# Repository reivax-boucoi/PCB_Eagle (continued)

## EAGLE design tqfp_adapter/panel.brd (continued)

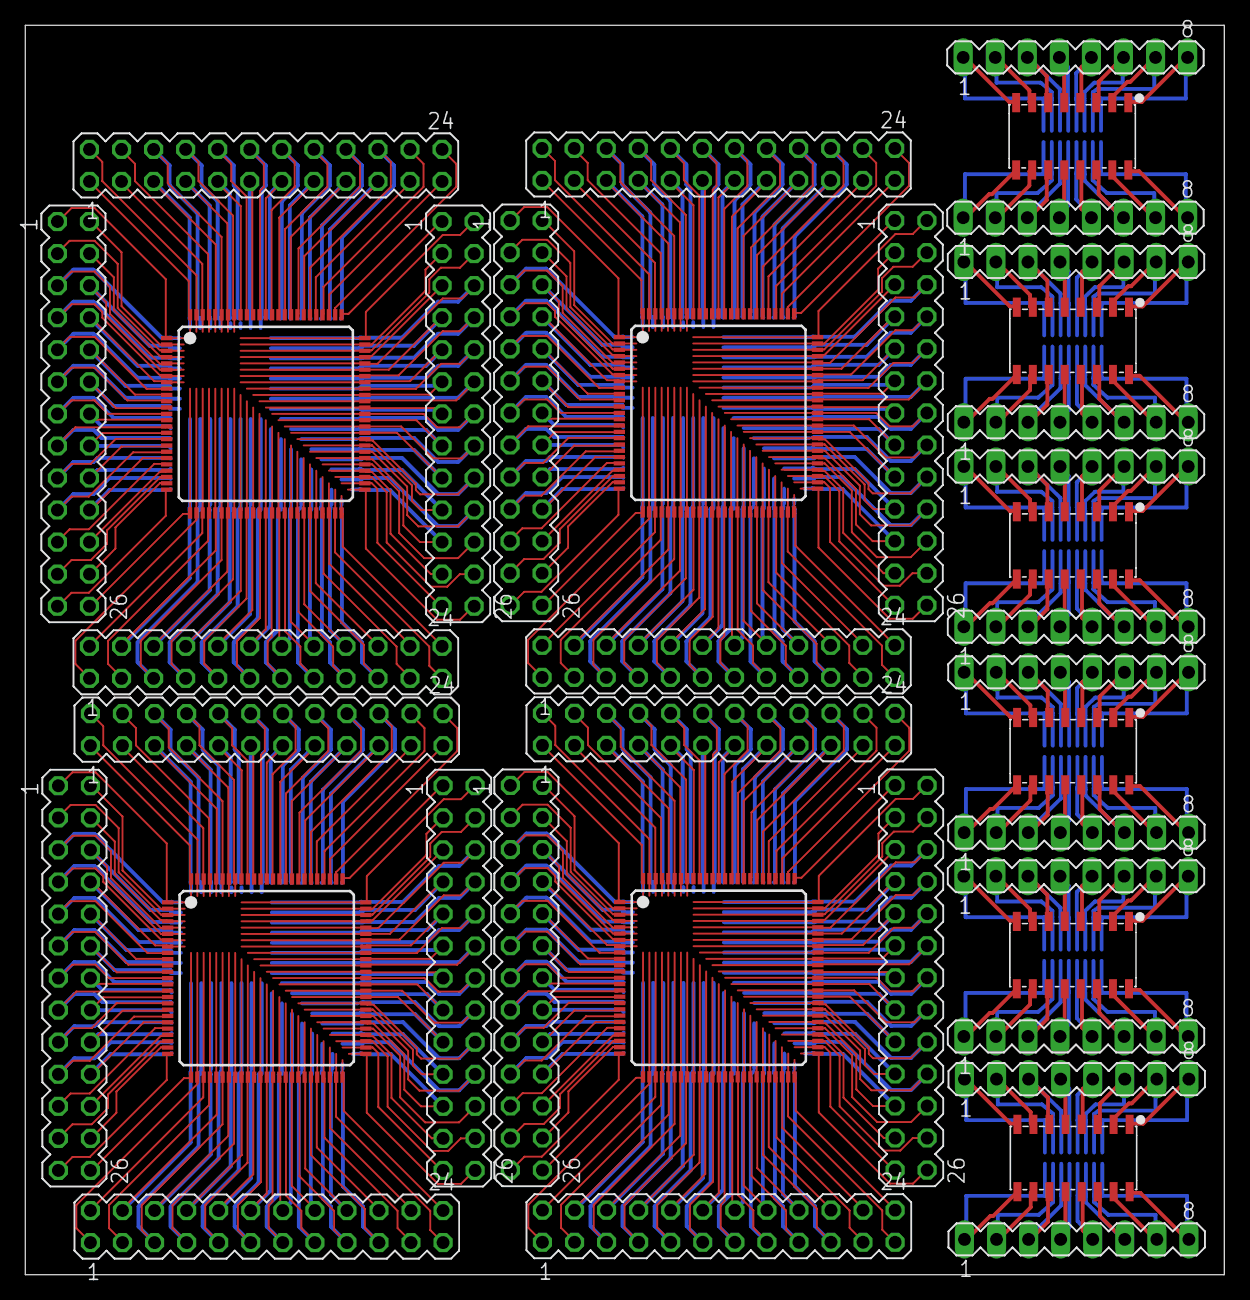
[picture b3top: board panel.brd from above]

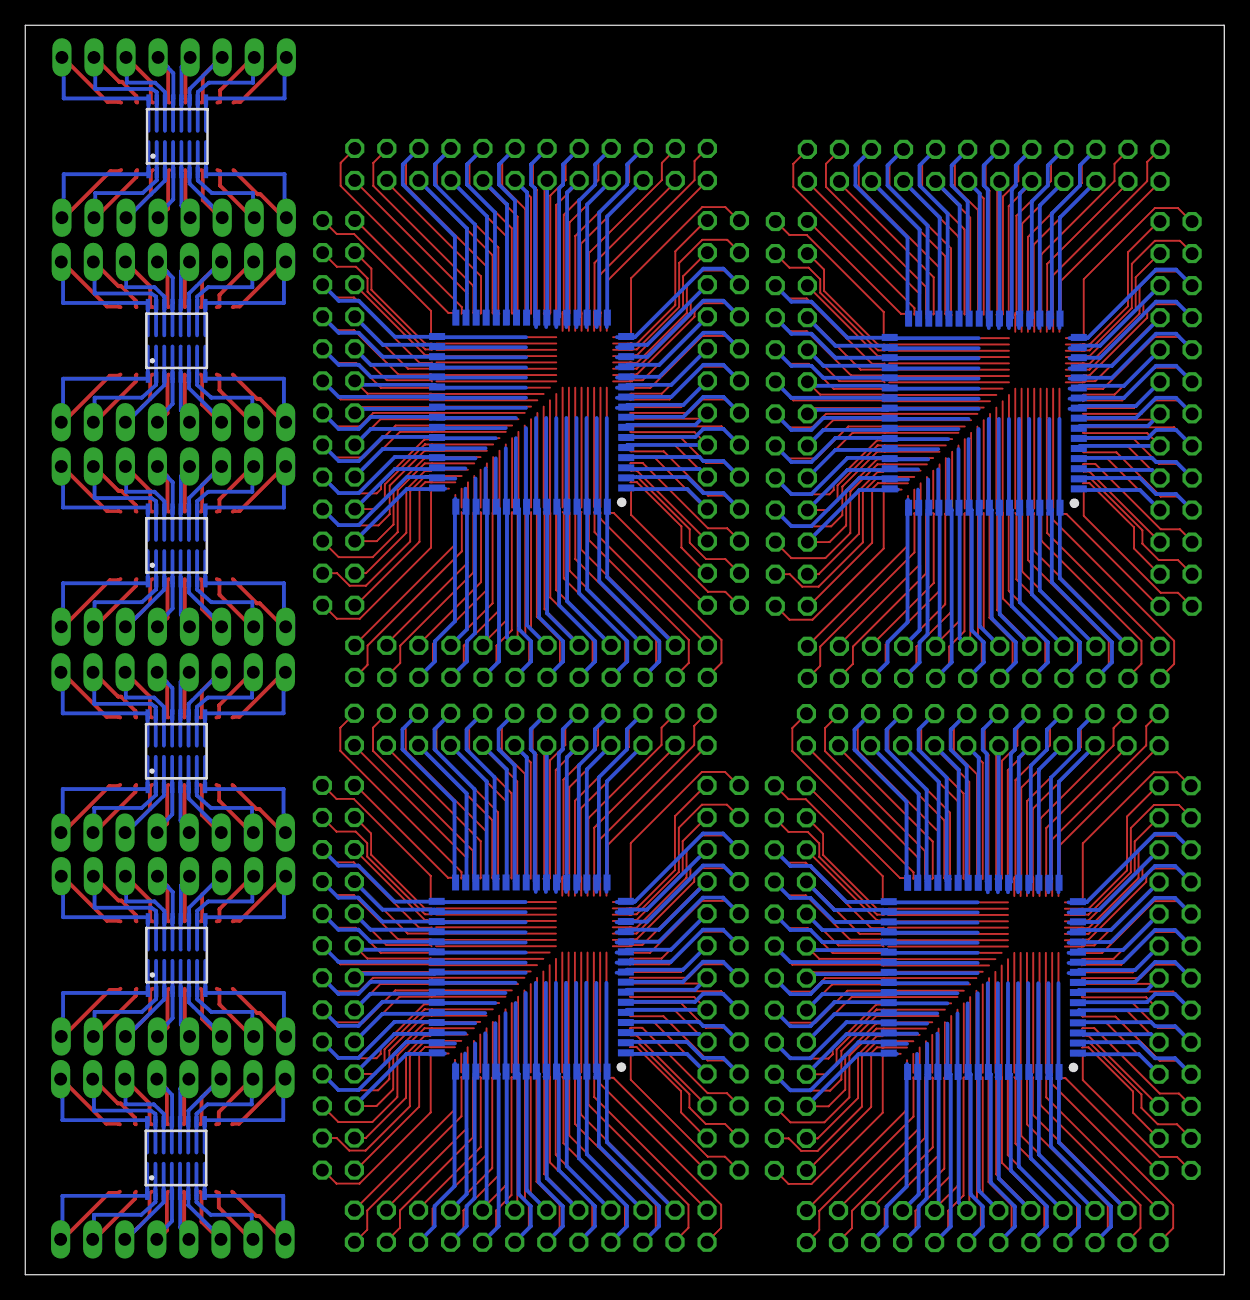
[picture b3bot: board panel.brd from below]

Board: 2 copper layers, 95.0 x 99.0 mm, 48 parts (10 on the bottom side), 486 nets.

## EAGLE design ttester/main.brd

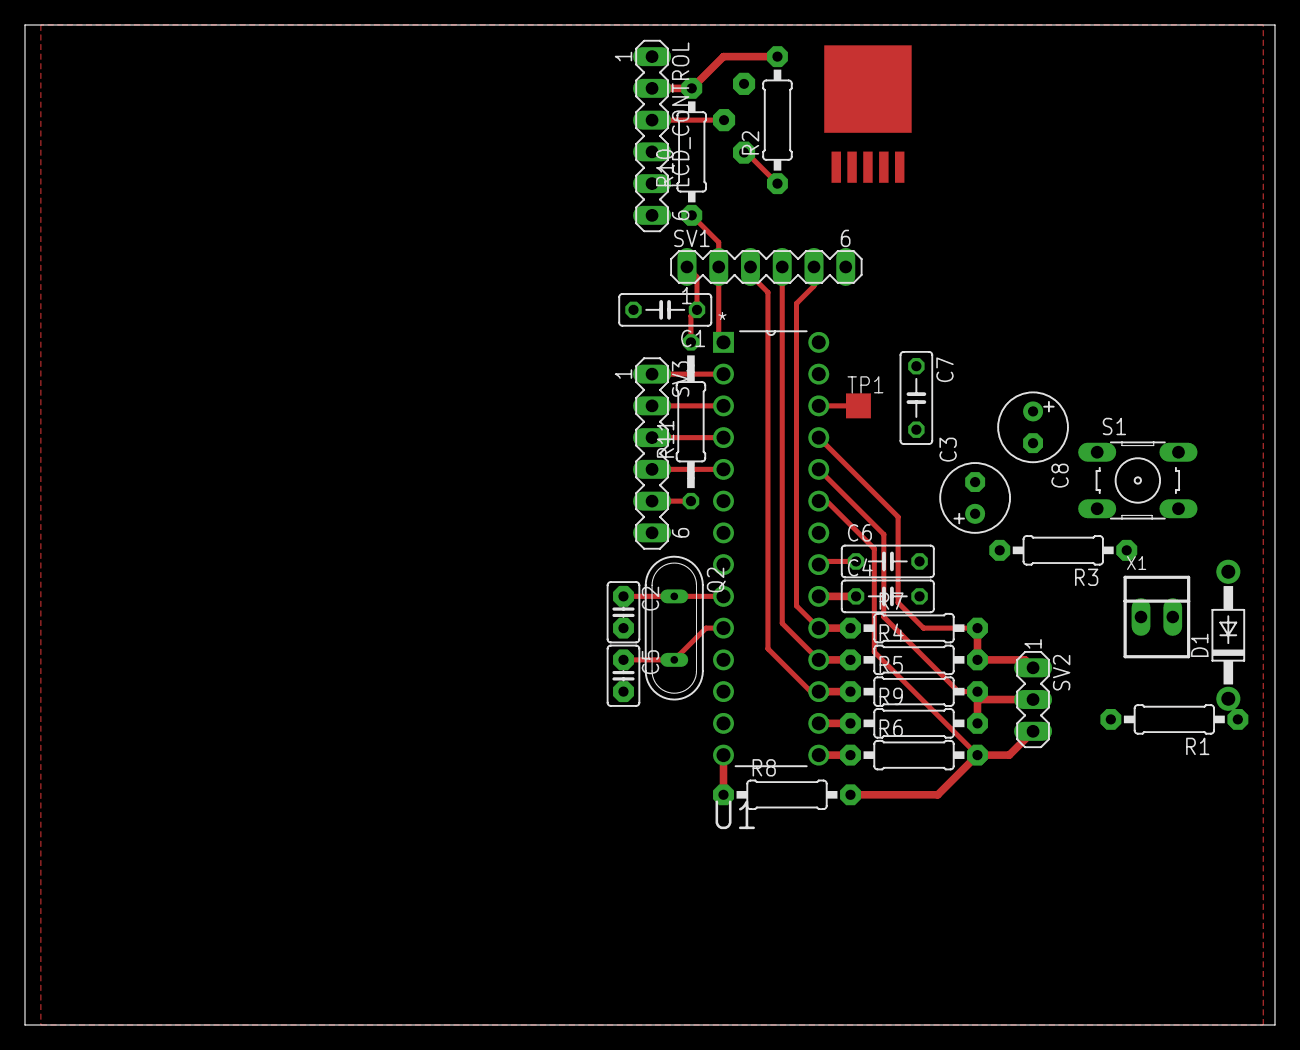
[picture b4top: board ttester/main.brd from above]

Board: 2 copper layers, 100.0 x 80.0 mm, 31 parts (1 on the bottom side), 28 nets.

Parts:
C1, C7: 100n; C050-025X075
C2, C5: 22p; C025-025X050
C3, C8: 10u; E2,5-6
C4: 10n; C050-025X075
C6: 1n; C050-025X075
D1: 1N4004; DO41-10
LCD_CONTROL: MA06-1
Q2: 16M; QS
R1: 1k; 0207/10
R2, R10: 10k; 0207/10
R3: 3k; 0207/10
R4, R8, R9: 680; 0207/10
R5, R6, R7: 470k; 0207/10
R11: 150; 0207/12
S1: B3F-10XX
SV1, SV3: MA06-1
SV2: MA03-1
TP1: TPTP20SQ; TP20SQ
U1: ATMEGA328P-PU; DIP254P762X457-28
U$1: POTAR
U$2: NJM2389; DPACK-5
X1: 22-23-2021

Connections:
+5V1: C8.+, D1.C, U$2.VIN
A: R11.1, SV3.5
AREF: C6.1, U1.21
D4: SV3.1, U1.2
D5: SV3.2, U1.3
D6: SV3.3, U1.4
D7: SV3.4, U1.5
E: LCD_CONTROL.6, U1.11
GND: C1.2, C2.2, C3.-, C4.2, C5.2, C6.2, C7.2, C8.-, LCD_CONTROL.1, R1.1, SV1.6, SV3.6, U1.8, U1.22, U$1.P$1, U$2.GND, X1.1
MISO: R4.1, SV1.4, U1.18
MOSI: R5.1, SV1.3, U1.17
unnamed: R2.1, U$1.P$2
unnamed: TP1.TP, U1.26
unnamed: R1.2, R3.1, U$2.VADJ
unnamed: R8.1, U1.14
unnamed: R6.1, U1.15
unnamed: R9.1, U1.16
RESET: R10.1, SV1.2, U1.1
RS: LCD_CONTROL.4, U1.6
SCK: R7.1, SV1.5, U1.19
TP1: R6.2, R8.2, SV2.3, U1.23
TP2: R5.2, R9.2, SV2.2, U1.24
TP3: R4.2, R7.2, SV2.1, U1.25
VBAT: D1.A, X1.2
VCC: C1.1, C3.+, C4.1, C7.1, LCD_CONTROL.2, R2.2, R3.2, R10.2, R11.2, SV1.1, U1.7, U1.20, U$2.VOUT, U$2.VOUT1
VO: LCD_CONTROL.3, U$1.WIPER
XTAL1: C2.1, Q2.1, U1.9
XTAL2: C5.1, Q2.2, U1.10

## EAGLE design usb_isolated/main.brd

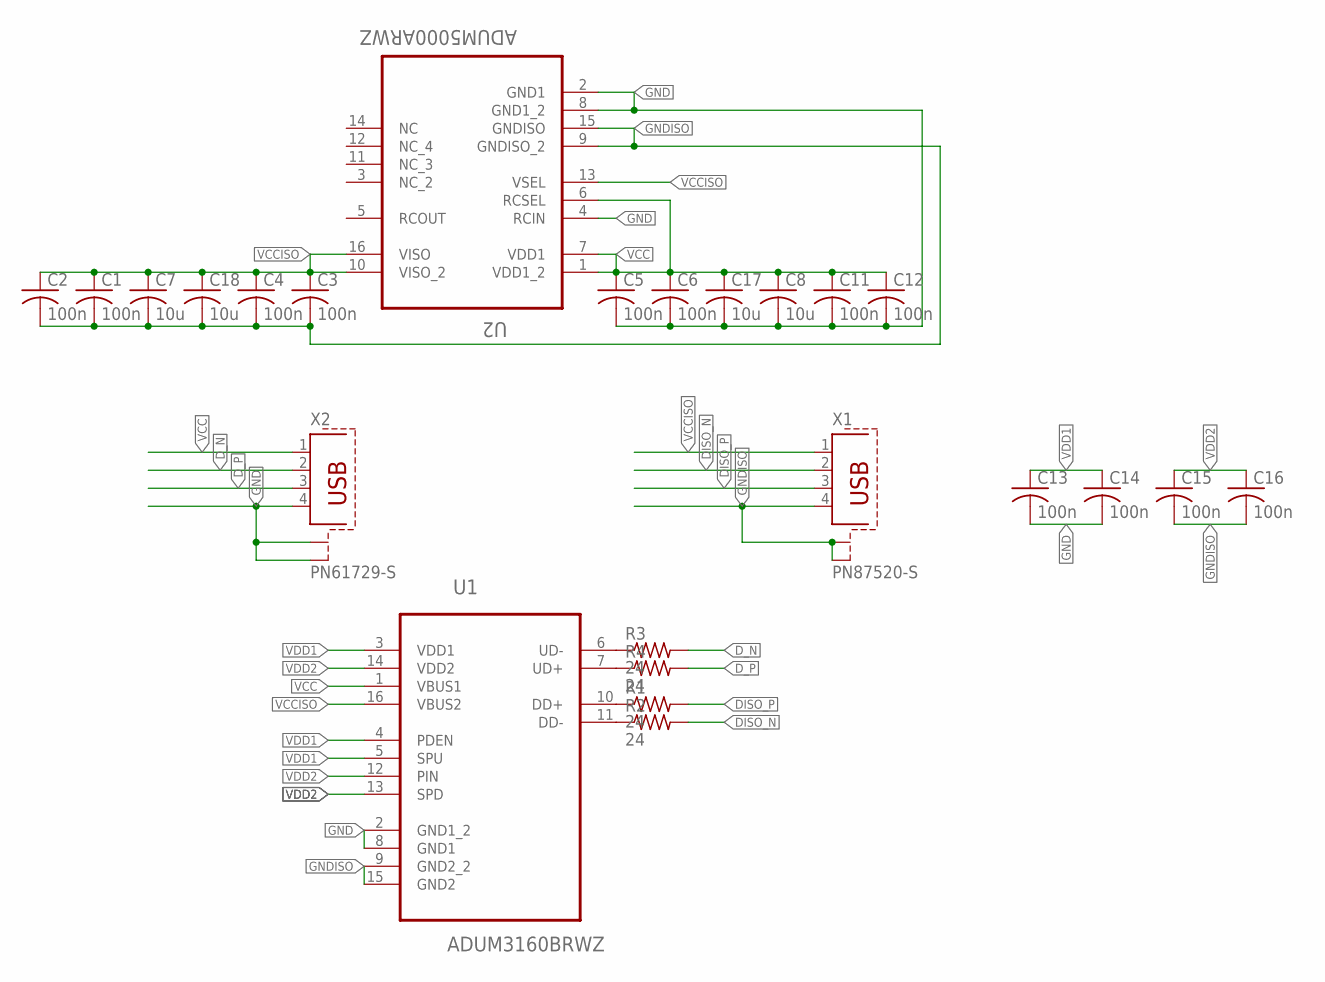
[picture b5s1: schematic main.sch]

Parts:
C1, C2, C3, C4, C5, C6, C11, C12, C13, C14, C15, C16: 100n; C0603
C7, C8, C17, C18: 10u; C025-025X050
R1, R2, R3, R4: 24; R0603
U1: ADUM3160BRWZ; SOIC127P1032X265-16N
U2: ADUM5000ARWZ; SOIC127P1032X265-16N
X1: PN87520-S
X2: PN61729-S

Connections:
DISO_N: R2.2, X1.2
DISO_P: R1.2, X1.3
D_N: R3.2, X2.2
D_P: R4.2, X2.3
GND: C5.2, C6.2, C8.2, C11.2, C12.2, C13.2, C14.2, C17.2, U1.2 (GND1_2), U1.8 (GND1), U2.2 (GND1), U2.4 (RCIN), U2.8 (GND1_2), X2.4, X2.S1, X2.S2
GNDISO: C1.2, C2.2, C3.2, C4.2, C7.2, C15.2, C16.2, C18.2, U1.9 (GND2_2), U1.15 (GND2), U2.9 (GNDISO_2), U2.15 (GNDISO), X1.4, X1.S1, X1.S2
unnamed: R1.1, U1.10 (DD+)
unnamed: R2.1, U1.11 (DD-)
unnamed: R3.1, U1.6 (UD-)
unnamed: R4.1, U1.7 (UD+)
VCC: C5.1, C6.1, C8.1, C11.1, C12.1, C17.1, U1.1 (VBUS1), U2.1 (VDD1_2), U2.6 (RCSEL), U2.7 (VDD1), X2.1
VCCISO: C1.1, C2.1, C3.1, C4.1, C7.1, C18.1, U1.16 (VBUS2), U2.10 (VISO_2), U2.13 (VSEL), U2.16 (VISO), X1.1
VDD1: C13.1, C14.1, U1.3 (VDD1), U1.4 (PDEN), U1.5 (SPU)
VDD2: C15.1, C16.1, U1.12 (PIN), U1.13 (SPD), U1.14 (VDD2)

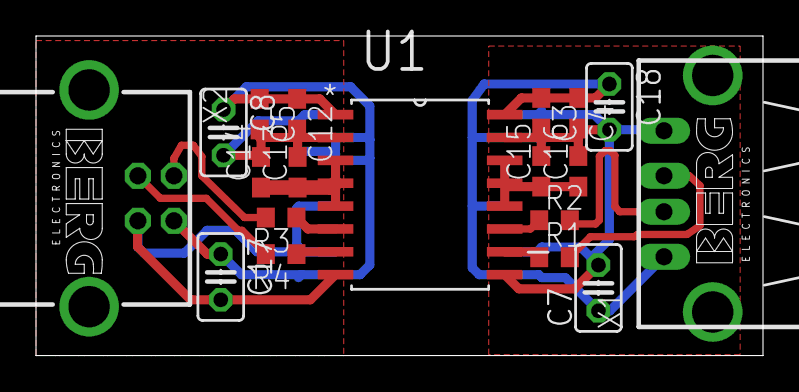
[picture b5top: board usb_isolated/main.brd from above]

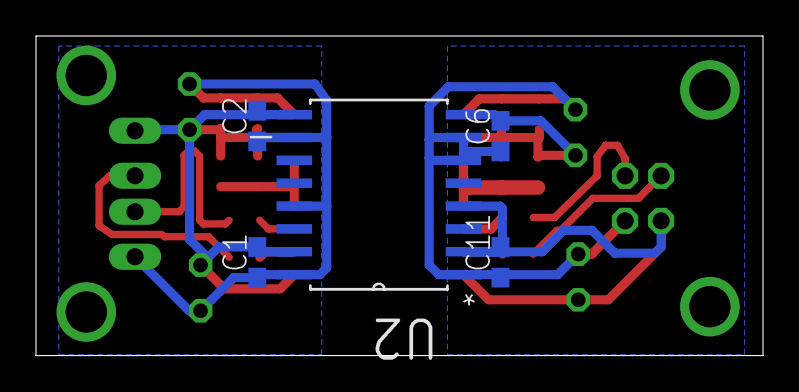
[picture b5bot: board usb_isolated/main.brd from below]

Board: 2 copper layers, 40.4 x 17.8 mm, 24 parts (5 on the bottom side), 14 nets.

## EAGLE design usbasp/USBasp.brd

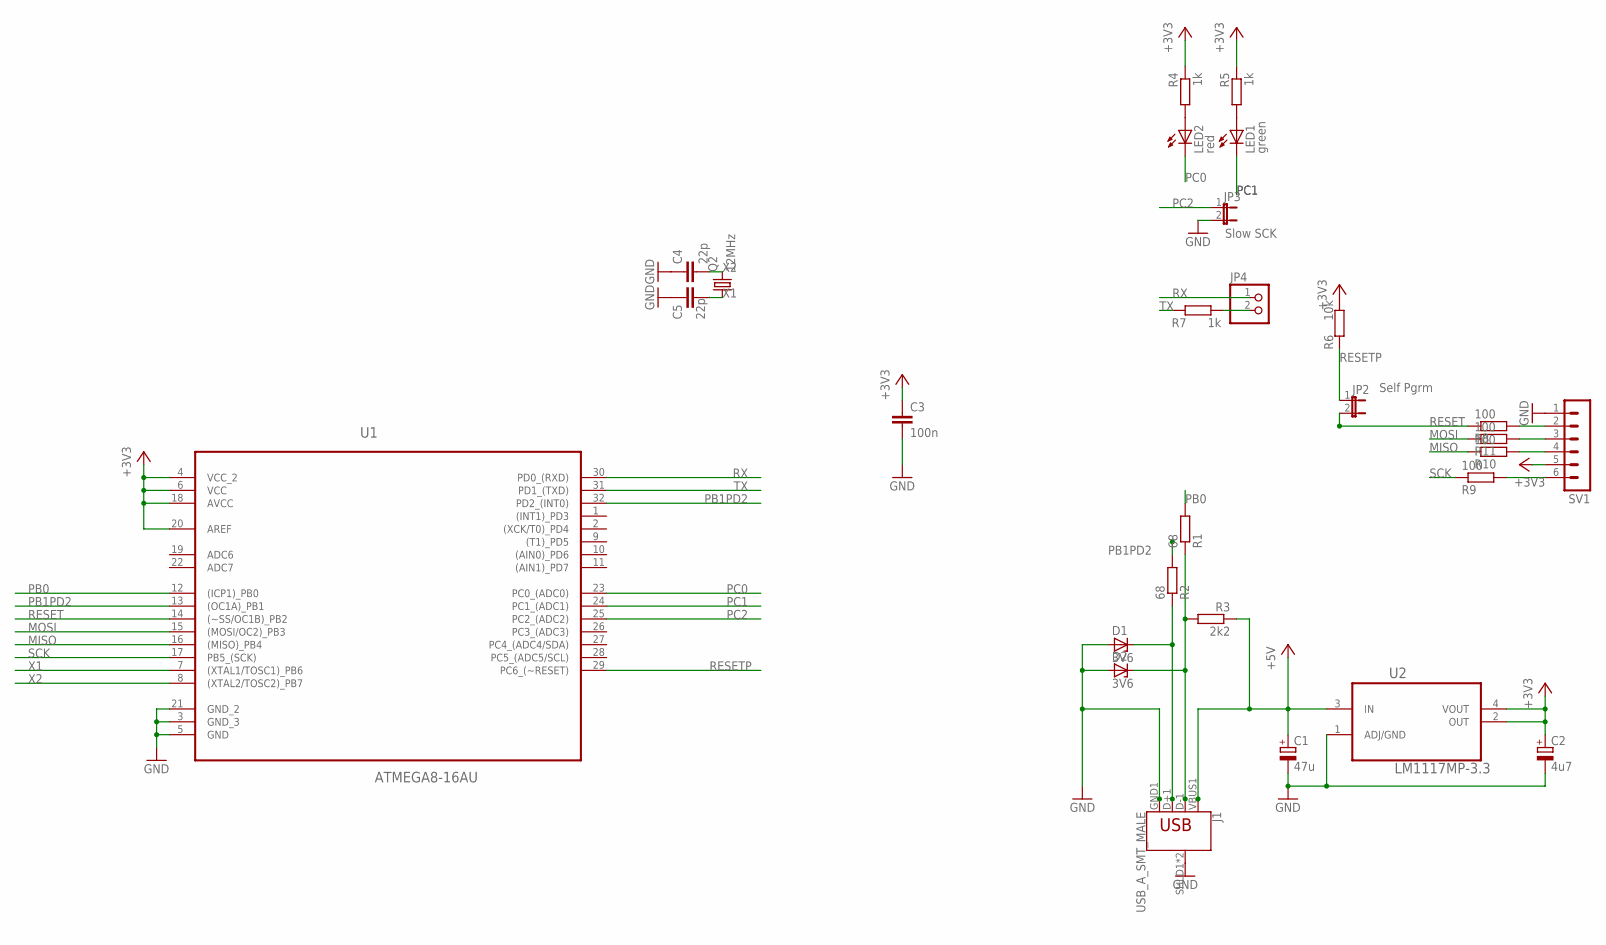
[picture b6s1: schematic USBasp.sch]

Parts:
C1: 47u; ETR4
C2: 4u7; E2,5-5
C3: 100n; C0603
C4: 22p; C0603
C5: 22p; C0504
D1, D2: 3V6; SOD80C
J1: USB_A_SMT_MALE; USB-A-SMT-MALE
JP2: Self Pgrm; JP1
JP3: Slow SCK; JP1
JP4: PINHD-1X2; 1X02
LED1: green; CHIP-LED0603
LED2: red; CHIP-LED0603
Q2: 12MHz; HC49/S
R1, R2: 68; R0603
R3: 2k2; R0603
R4, R5, R7: 1k; R0603
R6: 10k; R0603
R8, R9, R10, R11: 100; R0603
SV1: MA06-1
U1: ATMEGA8-16AU; QFP80P900X900X120-32N
U2: LM1117MP-3.3; SOT230P696X180-4N

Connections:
+3V3: C2.+, C3.1, R4.1, R5.1, R6.1, SV1.5, U1.4 (VCC_2), U1.6 (VCC), U1.18 (AVCC), U1.20 (AREF), U2.2 (OUT), U2.4 (VOUT)
+5V: C1.+, J1.VBUS1 (VBUS), R3.1, U2.3 (IN)
GND: C1.-, C2.-, C3.2, C4.1, C5.1, D1.A, D2.A, J1.GND1 (GND), J1.SHLD1 (SHIELD), J1.SHLD2 (SHIELD), JP3.2, SV1.1, U1.3 (GND_3), U1.5 (GND), U1.21 (GND_2), U2.1 (ADJ/GND)
MISO: R10.1, U1.16 ((MISO)_PB4)
MOSI: R11.1, U1.15 ((MOSI/OC2)_PB3)
unnamed: D2.C, J1.D-1 (D-), R1.1, R3.2
unnamed: D1.C, J1.D+1 (D+), R2.1
unnamed: JP4.2, R7.1
unnamed: LED2.A, R4.2
unnamed: R8.2, SV1.2
unnamed: R9.2, SV1.6
unnamed: R10.2, SV1.4
unnamed: R11.2, SV1.3
unnamed: LED1.A, R5.2
PB0: R1.2, U1.12 ((ICP1)_PB0)
PB1PD2: R2.2, U1.13 ((OC1A)_PB1), U1.32 (PD2_(INT0))
PC0: LED2.C, U1.23 (PC0_(ADC0))
PC1: LED1.C, U1.24 (PC1_(ADC1))
PC2: JP3.1, U1.25 (PC2_(ADC2))
RESET: JP2.2, R8.1, U1.14 ((~SS/OC1B)_PB2)
RESETP: JP2.1, R6.2, U1.29 (PC6_(~RESET))
RX: JP4.1, U1.30 (PD0_(RXD))
SCK: R9.1, U1.17 (PB5_(SCK))
TX: R7.2, U1.31 (PD1_(TXD))
X1: C5.2, Q2.1, U1.7 ((XTAL1/TOSC1)_PB6)
X2: C4.2, Q2.2, U1.8 ((XTAL2/TOSC2)_PB7)

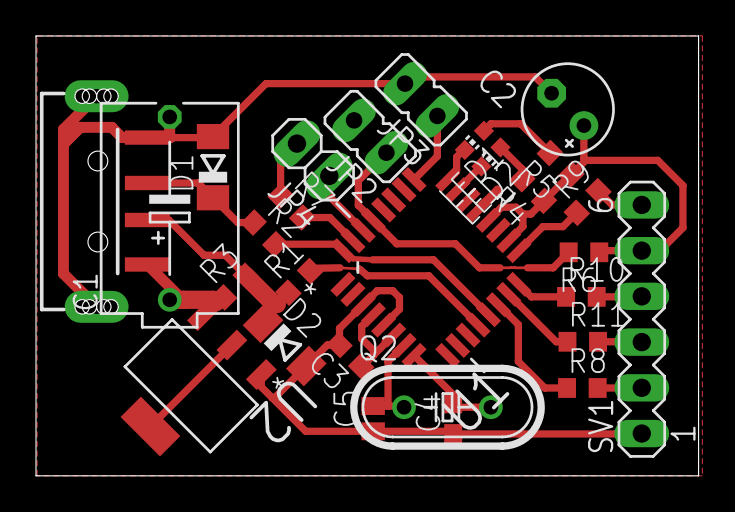
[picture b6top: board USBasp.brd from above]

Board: 2 copper layers, 36.8 x 24.4 mm, 28 parts (0 on the bottom side), 26 nets.

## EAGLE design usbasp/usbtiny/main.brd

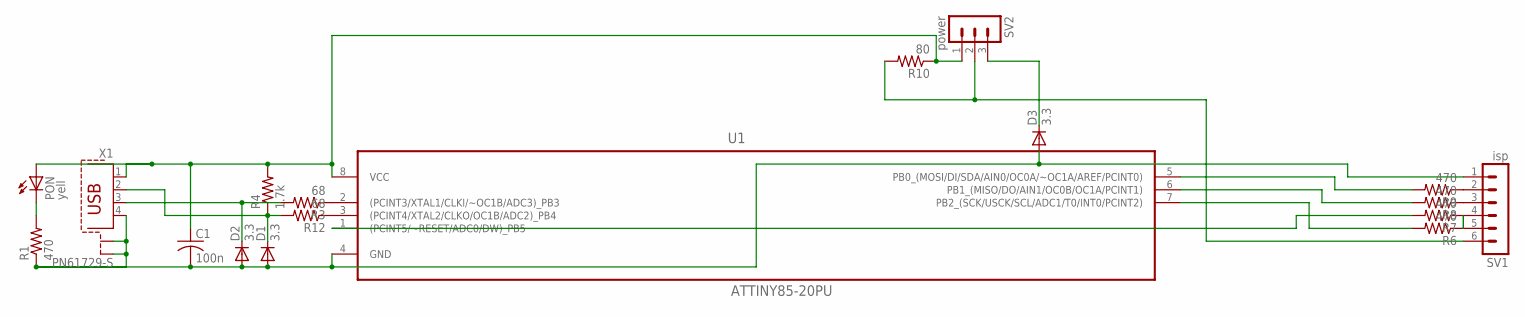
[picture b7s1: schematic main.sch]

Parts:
C1: 100n; C0805K
D1, D2, D3: 3.3; MELF-MLL41
PON: yell; LED5MM
R1, R6, R8, R9: 470; R0805
R3, R12: 68; R0805
R4: 1.7k; R0805
R7: 470; 0207/12
R10: 80; R0805
SV1: isp; MA06-1
SV2: power; MA03-1
U1: ATTINY85-20PU; DIP254P762X533-8
X1: PN61729-S

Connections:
unnamed: D1.C, R4.1, R12.2, X1.2
unnamed: R3.1, U1.2 ((PCINT3/XTAL1/CLKI/~OC1B/ADC3)_PB3)
unnamed: R12.1, U1.3 ((PCINT4/XTAL2/CLKO/OC1B/ADC2)_PB4)
unnamed: R9.2, U1.5 (PB0_(MOSI/DI/SDA/AIN0/OC0A/~OC1A/AREF/P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)
unnamed: D2.C, R3.2, X1.3
unnamed: C1.2, D1.A, D2.A, D3.A, R1.1, SV1.1, U1.4 (GND), X1.4, X1.S1, X1.S2
unnamed: R8.2, U1.6 (PB1_(MISO/DO/AIN1/OC0B/OC1A/PCINT1))
unnamed: R6.2, U1.7 (PB2_(SCK/USCK/SCL/ADC1/T0/INT0/PCINT2))
unnamed: R9.1, SV1.2
unnamed: PON.K (C), R1.2
unnamed: R7.2, U1.1 ((PCINT5/~RESET/ADC0/DW)_PB5)
unnamed: R8.1, SV1.3
unnamed: R7.1, SV1.5
unnamed: R6.1, SV1.4
unnamed: D3.C, SV2.3
unnamed: R10.2, SV1.6, SV2.2
unnamed: C1.1, PON.A, R4.2, R10.1, SV2.1, U1.8 (VCC), X1.1

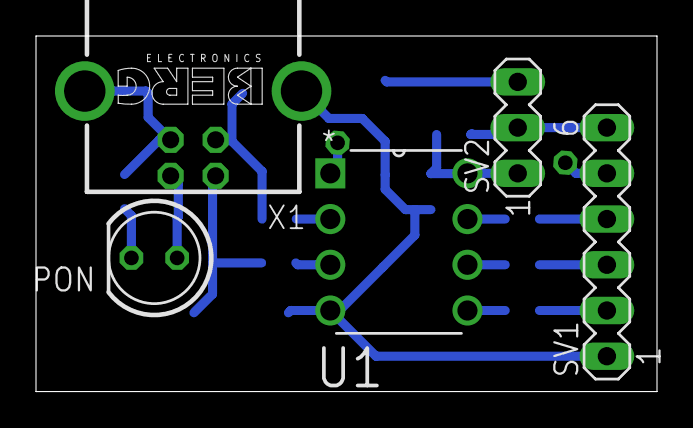
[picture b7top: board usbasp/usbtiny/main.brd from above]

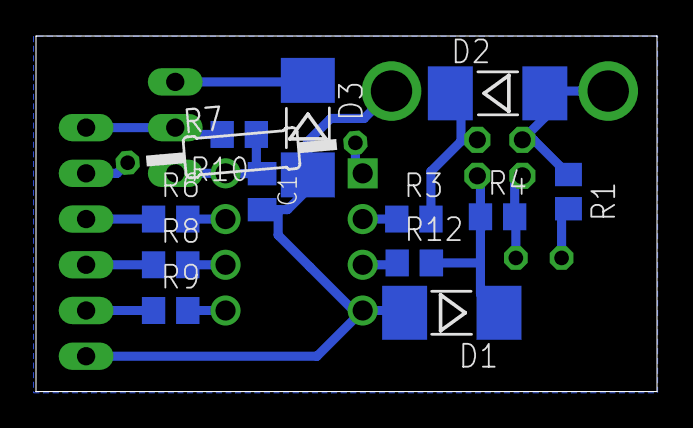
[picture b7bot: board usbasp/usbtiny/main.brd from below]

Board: 2 copper layers, 34.5 x 19.8 mm, 18 parts (13 on the bottom side), 17 nets.
